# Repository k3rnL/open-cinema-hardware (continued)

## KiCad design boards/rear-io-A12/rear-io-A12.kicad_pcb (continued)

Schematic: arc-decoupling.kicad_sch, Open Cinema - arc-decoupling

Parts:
C50: 100nF / U7 pin 1; C_0603_1608Metric; MPN CL10B104KB8NNNC
C51: 100nF / U7 pin 19; C_0603_1608Metric; MPN CL10B104KB8NNNC
C52: 100nF / U7 pin 49; C_0603_1608Metric; MPN CL10B104KB8NNNC
C53: 100nF / U7 pin 76; C_0603_1608Metric; MPN CL10B104KB8NNNC
C54: 100nF / U7 pin 77; C_0603_1608Metric; MPN CL10B104KB8NNNC
C55: 100nF / U7 pin 24; C_0603_1608Metric; MPN CL10B104KB8NNNC
C56: 100nF / U7 pin 25; C_0603_1608Metric; MPN CL10B104KB8NNNC
C57: 100nF / U7 pin 29; C_0603_1608Metric; MPN CL10B104KB8NNNC
C58: 100nF / U7 pin 34; C_0603_1608Metric; MPN CL10B104KB8NNNC
C59: 100nF / U7 pin 41; C_0603_1608Metric; MPN CL10B104KB8NNNC
C60: 100nF / U7 pin 21; C_0603_1608Metric; MPN CL10B104KB8NNNC
C61: 100nF / U7 pin 26; C_0603_1608Metric; MPN CL10B104KB8NNNC
C62: 100nF / U7 pin 47; C_0603_1608Metric; MPN CL10B104KB8NNNC
C63: 1uF 16V; C_0603_1608Metric; MPN CL10B105KO8NNNC
C64: 100nF; C_0603_1608Metric; MPN CL10B104KB8NNNC
J24: HDMI POWER FAULT / GND; PinHeader_1x02_P2.54mm_Vertical; MPN TSW-102-07-G-S
R52: 226k 1%; R_0603_1608Metric; MPN RC0603FR-07226KL
R53, R54: 10k; R_0603_1608Metric; MPN RC0603FR-0710KL

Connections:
+1V8_A: C57.1, C58.1, C59.1; also elsewhere on the board
+1V8_D: C50.1, C51.1, C52.1, C53.1, C54.1, C55.1, C56.1; also elsewhere on the board
+1V8_P: C60.1, C61.1; also elsewhere on the board
+3V3: C62.1, R54.2; also elsewhere on the board
+5V_IN: C63.1; also elsewhere on the board
GND: C50.2, C51.2, C52.2, C53.2, C54.2, C55.2, C56.2, C57.2, C58.2, C59.2, C60.2, C61.2, C62.2, C63.2, C64.2, J24.2, R52.2, R53.2; also elsewhere on the board
HDMI_5V: C64.1; also elsewhere on the board
HDMI_5V_EN: R53.1; also elsewhere on the board
HDMI_5V_FAULT_N: J24.1, R54.1; also elsewhere on the board
HDMI_ILIM: R52.1; also elsewhere on the board

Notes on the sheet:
A12 ARC STUDY - local decoupling and HDMI power control
Placement is a space study. Route decouplers at their named U7 pins with short ground vias.

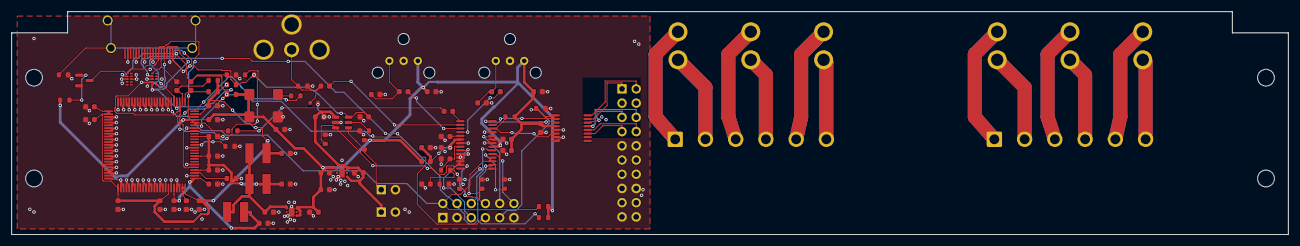
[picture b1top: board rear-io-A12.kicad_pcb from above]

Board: 4 copper layers, 228.0 x 39.8 mm, 98 parts (0 on the bottom side), 69 nets.

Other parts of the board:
H1, H2, H3, H4: D3 reference; MountingHole_D3_Reference_A8

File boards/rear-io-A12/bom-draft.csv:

ref,value,mpn,fp,dnp,source
U6,TLV75533PDRVR,TLV75533PDRVR,Package_SON:WSON-6-1EP_2x2mm_P0.65mm_EP1x1.6mm,False,https://www.ti.com/lit/ds/symlink/tlv755p.pdf
J21,5V regulated input,TSW-102-07-G-S,Connector_PinHeader_2.54mm:PinHeader_1x02_P2.54mm_Vertical,False,https://www.samtec.com/products/tsw-102-07-g-s
J20,PI CONTROL / NOT PI PINOUT,TSW-106-07-G-D,Connector_PinHeader_2.54mm:PinHeader_2x06_P2.54mm_Vertical,False,https://www.samtec.com/products/tsw-106-07-g-d
C1,4.7uF,CL10A475KO8NNNC,Capacitor_SMD:C_0603_1608Metric,False,
C2,4.7uF,CL10A475KO8NNNC,Capacitor_SMD:C_0603_1608Metric,False,
C3,10uF,CL10A106KP8NNNC,Capacitor_SMD:C_0603_1608Metric,False,
R1,4.7k,RC0603FR-074K7L,Resistor_SMD:R_0603_1608Metric,True,
R2,4.7k,RC0603FR-074K7L,Resistor_SMD:R_0603_1608Metric,True,
R3,10k,RC0603FR-0710KL,Resistor_SMD:R_0603_1608Metric,False,
R6,10k,RC0603FR-0710KL,Resistor_SMD:R_0603_1608Metric,False,
U1,CS8416K-CZZR,CS8416K-CZZR,Package_SO:TSSOP-28_4.4x9.7mm_P0.65mm,False,https://statics.cirrus.com/pubs/proDatasheet/CS8416_DS578F5.pdf
J7,FCR684205R,FCR684205R,OpenCinema_Connectors:Cliff_FCR684205R,False,
C11,100nF,CL10B104KB8NNNC,Capacitor_SMD:C_0603_1608Metric,False,
C13,100nF,CL10B104KB8NNNC,Capacitor_SMD:C_0603_1608Metric,False,
C15,30pF C0G,CL10C300JB8NNNC,Capacitor_SMD:C_0603_1608Metric,False,
J8,FCR684205R,FCR684205R,OpenCinema_Connectors:Cliff_FCR684205R,False,
C12,100nF,CL10B104KB8NNNC,Capacitor_SMD:C_0603_1608Metric,False,
C14,100nF,CL10B104KB8NNNC,Capacitor_SMD:C_0603_1608Metric,False,
C16,30pF C0G,CL10C300JB8NNNC,Capacitor_SMD:C_0603_1608Metric,False,
J9,RCJ-011,RCJ-011,OpenCinema_Connectors:SameSky_RCJ_011_Horizontal_A8,False,
R10,75R 1%,RC0603FR-0775RL,Resistor_SMD:R_0603_1608Metric,False,
C17,10nF,CL10B103KB8NNNC,Capacitor_SMD:C_0603_1608Metric,False,
C18,10nF,CL10B103KB8NNNC,Capacitor_SMD:C_0603_1608Metric,False,
FB1,600R @100MHz,BLM18AG601SN1D,Inductor_SMD:L_0603_1608Metric,False,
C19,100nF,CL10B104KB8NNNC,Capacitor_SMD:C_0603_1608Metric,False,
C20,10uF,CL10A106KP8NNNC,Capacitor_SMD:C_0603_1608Metric,False,
C21,100nF,CL10B104KB8NNNC,Capacitor_SMD:C_0603_1608Metric,False,
C22,100nF,CL10B104KB8NNNC,Capacitor_SMD:C_0603_1608Metric,False,
C23,1nF C0G,CL10C102JB8NNNC,Capacitor_SMD:C_0603_1608Metric,False,
C24,22nF X7R,CL10B223KB8NNNC,Capacitor_SMD:C_0603_1608Metric,False,
R11,3k 1%,RC0603FR-073KL,Resistor_SMD:R_0603_1608Metric,False,
R12,47k,RC0603FR-0747KL,Resistor_SMD:R_0603_1608Metric,False,
R13,47k,RC0603FR-0747KL,Resistor_SMD:R_0603_1608Metric,False,
R14,10k,RC0603FR-0710KL,Resistor_SMD:R_0603_1608Metric,False,
R15,10k,RC0603FR-0710KL,Resistor_SMD:R_0603_1608Metric,False,
U4,DS90LV047ATMTC/NOPB,DS90LV047ATMTC/NOPB,Package_SO:TSSOP-16_4.4x5mm_P0.65mm,False,https://www.ti.com/lit/ds/symlink/ds90lv047a.pdf
J22,3 LVDS PAIRS / PROVISIONAL,TSW-110-07-G-D,Connector_PinHeader_2.54mm:PinHeader_2x10_P2.54mm_Vertical,False,https://www.samtec.com/products/tsw-110-07-g-d
C32,100nF,CL10B104KB8NNNC,Capacitor_SMD:C_0603_1608Metric,False,
SP1,KLS1-WP-6P-03B / UNQUALIFIED,L-KLS1-WP-6P-03B-B/R,OpenCinema_Connectors:KLS1_WP_6P_03B_Horizontal_A8,False,
J31,AMP WIRE SOLDER PADS,PCB_SOLDER_PADS_1SQMM,Connector_Wire:SolderWire-1sqmm_1x06_P5.4mm_D1.4mm_OD2.7mm,False,
SP2,KLS1-WP-6P-03B / UNQUALIFIED,L-KLS1-WP-6P-03B-B/R,OpenCinema_Connectors:KLS1_WP_6P_03B_Horizontal_A8,False,
J32,AMP WIRE SOLDER PADS,PCB_SOLDER_PADS_1SQMM,Connector_Wire:SolderWire-1sqmm_1x06_P5.4mm_D1.4mm_OD2.7mm,False,
U7,ADV7511KSTZ / ARC candidate,ADV7511KSTZ,Package_QFP:LQFP-100_14x14mm_P0.5mm,False,https://www.analog.com/media/en/technical-documentation/user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
R40,887R 1%,RC0603FR-07887RL,Resistor_SMD:R_0603_1608Metric,False,
R41,2k 1%,RC0603FR-072KL,Resistor_SMD:R_0603_1608Metric,False,
R42,2k 1%,RC0603FR-072KL,Resistor_SMD:R_0603_1608Metric,False,
Y1,12 MHz / ASV-12.000MHZ-E-T,ASV-12.000MHZ-E-T,Oscillator:Oscillator_SMD_Abracon_ASV-4Pin_7.0x5.1mm,False,https://abracon.com/Oscillators/ASV.pdf
R43,33R,RC0603FR-0733RL,Resistor_SMD:R_0603_1608Metric,False,
C40,100nF,CL10B104KB8NNNC,Capacitor_SMD:C_0603_1608Metric,False,
J10,10029449-001RLF / ARC ONLY,10029449-001RLF,OpenCinema_Connectors:HDMI_A_Amphenol_10029449-x01xLF_Horizontal,False,
C41,1uF 16V,CL10B105KO8NNNC,Capacitor_SMD:C_0603_1608Metric,False,
C42,1uF 16V,CL10B105KO8NNNC,Capacitor_SMD:C_0603_1608Metric,False,
R44,49.9R 1%,RC0603FR-0749R9L,Resistor_SMD:R_0603_1608Metric,False,
R45,49.9R 1%,RC0603FR-0749R9L,Resistor_SMD:R_0603_1608Metric,False,
R46,10k,RC0603FR-0710KL,Resistor_SMD:R_0603_1608Metric,False,
R47,2k 1%,RC0603FR-072KL,Resistor_SMD:R_0603_1608Metric,False,
R48,2k 1%,RC0603FR-072KL,Resistor_SMD:R_0603_1608Metric,False,
R49,27k 1%,RC0603FR-0727KL,Resistor_SMD:R_0603_1608Metric,False,
D1,"BAS116,215","BAS116,215",Package_TO_SOT_SMD:SOT-23,False,https://assets.nexperia.com/documents/data-sheet/BAS116.pdf
R50,33R,RC0603FR-0733RL,Resistor_SMD:R_0603_1608Metric,False,
C43,100nF,CL10B104KB8NNNC,Capacitor_SMD:C_0603_1608Metric,False,
R51,0R / chassis bond DNP,RC0603JR-070RL,Resistor_SMD:R_0603_1608Metric,True,
U10,TPD4E05U06DQAR,TPD4E05U06DQAR,Package_SON:USON-10_2.5x1.0mm_P0.5mm,False,https://www.ti.com/lit/ds/symlink/tpd4e05u06.pdf
U11,TPD4E05U06DQAR,TPD4E05U06DQAR,Package_SON:USON-10_2.5x1.0mm_P0.5mm,False,https://www.ti.com/lit/ds/symlink/tpd4e05u06.pdf
U8,TLV75518PDRVR,TLV75518PDRVR,Package_SON:WSON-6-1EP_2x2mm_P0.65mm_EP1x1.6mm,False,https://www.ti.com/lit/ds/symlink/tlv755p.pdf
C44,4.7uF,CL10A475KO8NNNC,Capacitor_SMD:C_0603_1608Metric,False,
C45,4.7uF,CL10A475KO8NNNC,Capacitor_SMD:C_0603_1608Metric,False,
L1,10uH / SRN4018-100M,SRN4018-100M,Inductor_SMD:L_Bourns-SRN4018,False,https://www.bourns.com/docs/product-datasheets/srn4018.pdf
C46,10uF,CL10A106KP8NNNC,Capacitor_SMD:C_0603_1608Metric,False,
L2,10uH / SRN4018-100M,SRN4018-100M,Inductor_SMD:L_Bourns-SRN4018,False,https://www.bourns.com/docs/product-datasheets/srn4018.pdf
C47,10uF,CL10A106KP8NNNC,Capacitor_SMD:C_0603_1608Metric,False,
L3,10uH / SRN4018-100M,SRN4018-100M,Inductor_SMD:L_Bourns-SRN4018,False,https://www.bourns.com/docs/product-datasheets/srn4018.pdf
C48,10uF,CL10A106KP8NNNC,Capacitor_SMD:C_0603_1608Metric,False,
C50,100nF / U7 pin 1,CL10B104KB8NNNC,Capacitor_SMD:C_0603_1608Metric,False,
C51,100nF / U7 pin 19,CL10B104KB8NNNC,Capacitor_SMD:C_0603_1608Metric,False,
C52,100nF / U7 pin 49,CL10B104KB8NNNC,Capacitor_SMD:C_0603_1608Metric,False,
C53,100nF / U7 pin 76,CL10B104KB8NNNC,Capacitor_SMD:C_0603_1608Metric,False,
C54,100nF / U7 pin 77,CL10B104KB8NNNC,Capacitor_SMD:C_0603_1608Metric,False,
C55,100nF / U7 pin 24,CL10B104KB8NNNC,Capacitor_SMD:C_0603_1608Metric,False,
C56,100nF / U7 pin 25,CL10B104KB8NNNC,Capacitor_SMD:C_0603_1608Metric,False,
C57,100nF / U7 pin 29,CL10B104KB8NNNC,Capacitor_SMD:C_0603_1608Metric,False,
C58,100nF / U7 pin 34,CL10B104KB8NNNC,Capacitor_SMD:C_0603_1608Metric,False,
C59,100nF / U7 pin 41,CL10B104KB8NNNC,Capacitor_SMD:C_0603_1608Metric,False,
C60,100nF / U7 pin 21,CL10B104KB8NNNC,Capacitor_SMD:C_0603_1608Metric,False,
C61,100nF / U7 pin 26,CL10B104KB8NNNC,Capacitor_SMD:C_0603_1608Metric,False,
C62,100nF / U7 pin 47,CL10B104KB8NNNC,Capacitor_SMD:C_0603_1608Metric,False,
U9,TPS2553DBVR,TPS2553DBVR,Package_TO_SOT_SMD:SOT-23-6,False,https://www.ti.com/lit/ds/symlink/tps2553.pdf
R52,226k 1%,RC0603FR-07226KL,Resistor_SMD:R_0603_1608Metric,False,
R53,10k,RC0603FR-0710KL,Resistor_SMD:R_0603_1608Metric,False,
R54,10k,RC0603FR-0710KL,Resistor_SMD:R_0603_1608Metric,False,
C63,1uF 16V,CL10B105KO8NNNC,Capacitor_SMD:C_0603_1608Metric,False,
C64,100nF,CL10B104KB8NNNC,Capacitor_SMD:C_0603_1608Metric,False,
J24,HDMI POWER FAULT / GND,TSW-102-07-G-S,Connector_PinHeader_2.54mm:PinHeader_1x02_P2.54mm_Vertical,False,https://www.samtec.com/products/tsw-102-07-g-s
D2,TPD1E10B06DYAR,TPD1E10B06DYAR,Diode_SMD:D_SOD-523,False,https://www.ti.com/lit/ds/symlink/tpd1e10b06.pdf

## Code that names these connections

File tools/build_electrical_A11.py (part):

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# Power / controls: GPIO numbering intentionally unassigned. Both boards must be powered together.
part('power-control','U6','LDO','TLV75533PDBVR',{1:'+5V_IN',2:'GND',3:'+5V_IN',4:None,5:'+3V3'},105,55,154,128,mpn='TLV75533PDBVR',source='https://www.ti.com/lit/ds/symlink/tlv755p.pdf')
part('power-control','J21','CON2','5V regulated input',{1:'+5V_IN',2:'GND'},40,55,165,130,mpn='HEADER_1X02_P2.54_PROVISIONAL')
part('power-control','J20','CON12','PI CONTROL / NOT PI PINOUT',{1:'GND',2:'I2C_SDA',3:'GND',4:'I2C_SCL',5:'CS_RESET_N',6:'CS_INT',7:'ADV_INT',8:'HDMI_5V_EN',9:'LVDS_EN',10:'CS_RMCK_MON',11:'GND',12:'CS_RERR'},270,65,151,134,90,mpn='HEADER_2X06_P2.54_PROVISIONAL')
for i,net in enumerate(['+5V_IN','GND','+3V3_A']):part('power-control','#FLG'+str(i+1),'PWR_FLAG','POWER PROVIDED',{1:net},340,100+i*35)
for i,(net,val,bx,by) in enumerate([('+5V_IN','4.7uF',159,128),('+3V3','4.7uF',149,128),('+3V3','10uF',145,128)],1):passive('power-control','C'+str(i),'C',val,net,'GND',65+(i-1)*75,110,bx,by)
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passive('spdif','FB1','FB','600R @100MHz','+3V3','+3V3_A',310,145,132,123,'BLM18AG601SN1D')
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# CS_RERR monitor test point is routed to a labelled test pad in later layout; no automatic fault gate yet.
# One receiver selects all four S/PDIF sources. Only three LVDS pairs are used.
lvds={1:'LVDS_EN',8:'GND',4:'+3V3',5:'GND',2:'SPDIF_BCLK',3:'SPDIF_LRCLK',6:'SPDIF_D0',7:'GND',15:'LVDS_BCLK_P',16:'LVDS_BCLK_N',14:'LVDS_LRCLK_P',13:'LVDS_LRCLK_N',11:'LVDS_D0_P',12:'LVDS_D0_N',10:None,9:None}
part('selection-lvds','U4','LVDS','DS90LV047ATMTC/NOPB',lvds,135,80,100,125,source='https://www.ti.com/lit/ds/symlink/ds90lv047a.pdf')
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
